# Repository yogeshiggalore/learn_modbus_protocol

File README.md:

# learn_modbus_protocol
learn Modbus protocol
Hardware design

PCB view

3D view

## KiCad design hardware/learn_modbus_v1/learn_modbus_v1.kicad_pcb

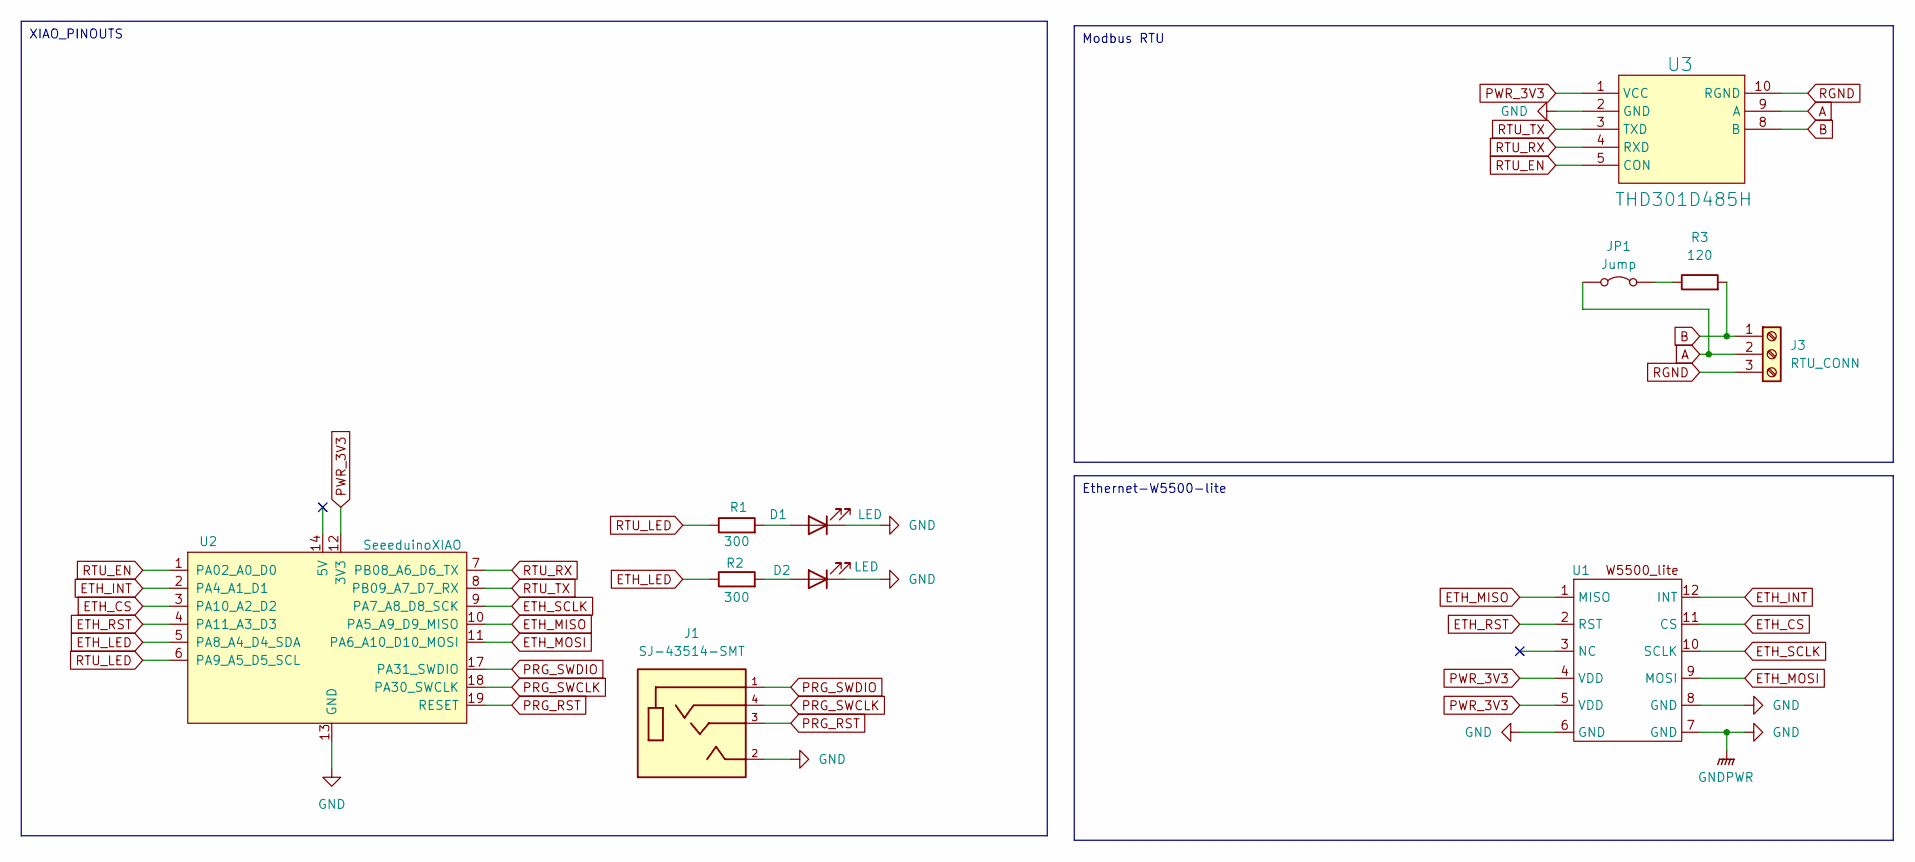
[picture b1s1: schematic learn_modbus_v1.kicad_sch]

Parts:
D1, D2: LED; LED_0805_2012Metric_Pad1.15x1.40mm_HandSolder
J1: SJ-43514-SMT; CUI_SJ-43514-SMT
J3: RTU_CONN; TerminalBlock_RND_205-00002_1x03_P5.00mm_Horizontal
JP1: Jump; TestPoint_2Pads_Pitch2.54mm_Drill0.8mm
R1, R2: 300; R_0805_2012Metric_Pad1.20x1.40mm_HandSolder
R3: 120; R_0805_2012Metric_Pad1.20x1.40mm_HandSolder
U1: w5500_lite
U2: SeeeduinoXIAO; Seeeduino_Xiao
U3: THD301D485H; TDH5(3)01D485H

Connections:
A: J3.2, JP1.1 (A), U3.9 (A)
B: J3.1, R3.2, U3.8 (B)
ETH_CS: U1.11 (CS), U2.3 (PA10_A2_D2)
ETH_INT: U1.12 (INT), U2.2 (PA4_A1_D1)
ETH_LED: R2.1, U2.5 (PA8_A4_D4_SDA)
ETH_MISO: U1.1 (MISO), U2.10 (PA5_A9_D9_MISO)
ETH_MOSI: U1.9 (MOSI), U2.11 (PA6_A10_D10_MOSI)
ETH_RST: U1.2 (RST), U2.4 (PA11_A3_D3)
ETH_SCLK: U1.10 (SCLK), U2.9 (PA7_A8_D8_SCK)
GND: D1.1 (K), D2.1 (K), J1.2, U1.6 (GND), U1.7 (GND), U1.8 (GND), U2.13 (GND), U2.20 (GND), U3.2 (GND)
unnamed: D1.2 (A), R1.2
unnamed: D2.2 (A), R2.2
unnamed: JP1.2 (B), R3.1
PRG_RST: J1.3, U2.19 (RESET)
PRG_SWCLK: J1.4, U2.18 (PA30_SWCLK)
PRG_SWDIO: J1.1, U2.17 (PA31_SWDIO)
PWR_3V3: U1.4 (VDD), U1.5 (VDD), U2.12 (3V3), U3.1 (VCC)
RGND: J3.3, U3.10 (RGND)
RTU_EN: U2.1 (PA02_A0_D0), U3.5 (CON)
RTU_LED: R1.1, U2.6 (PA9_A5_D5_SCL)
RTU_RX: U2.7 (PB08_A6_D6_TX), U3.4 (RXD)
RTU_TX: U2.8 (PB09_A7_D7_RX), U3.3 (TXD)

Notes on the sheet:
Ethernet-W5500-lite
Modbus RTU
XIAO_PINOUTS

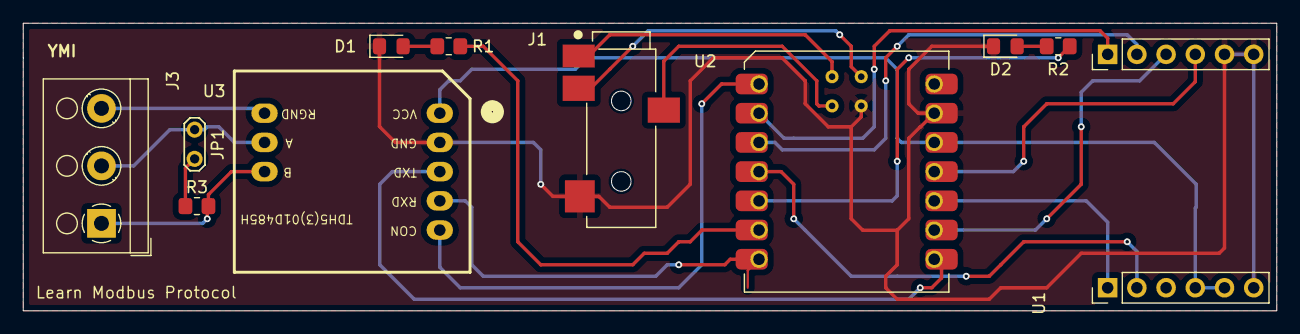
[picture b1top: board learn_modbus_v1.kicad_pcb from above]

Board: 2 copper layers, 109.0 x 25.0 mm, 11 parts (0 on the bottom side), 22 nets.

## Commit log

2024-07-21 init
    initial commit
2024-07-21 hardware init
    hardware init
2024-07-21 PCB update
    PCB update
2024-07-22 gerber generated
    gerber generated
